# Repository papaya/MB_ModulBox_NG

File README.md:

# MB_ModulBox_NG — Contrôleur MIDI Modulaire (Écosystème MIDIbox NG)

> **Construisez votre propre contrôleur MIDI modulaire.**  
> MB_ModulBox_NG rassemble des front-ends originaux et des ré-implémentations KiCad de modules MIDIbox. Les niveaux de validation et les fichiers de fabrication disponibles varient d'une carte à l'autre : consulter la matrice ci-dessous avant toute commande.

---

## 🎯 Le projet en bref

MB_ModulBox_NG est une **bibliothèque de cartes de contrôle physiques** pour le système MIDIbox NG. Les sources, schémas, PCB et fichiers de fabrication ne sont pas tous disponibles pour chaque carte. Les états indiqués ci-dessous décrivent les fichiers présents dans le dépôt, pas une certification de fabrication.

Les **modules standards MIDIbox** (AIN, DIN, DOUT, Core, IO) sont fournis en **bonus de référence** pour alimenter ces front-ends — ils ne sont pas le cœur du projet. L'essence de ce dépôt, ce sont les **`custom-frontends/`**.

## 🧩 Les modules: Custom Front-ends — le cœur du dépôt

| Apercu | Module | Dossier | Fonction / bus | Fichiers de fabrication versionnés | État documentaire |
|---|---|---|---|---|---|
|   | encoders-led-rgb | [`custom-frontends/encoders-led-rgb/`](custom-frontends/encoders-led-rgb/) | 8 PEC16, DIN, 128 WS2812 | BOM/positions/netlist uniquement ; pas de Gerbers de sous-cartes | Prototype ; DRC et séparation à revoir |
|   | 4x-faders | [`custom-frontends/4x-faders/`](custom-frontends/4x-faders/) | 8 faders, AIN (`+3V0`) | Gerbers + perçages pour deux PCB ; pas de BOM dans `production/` | Fichiers disponibles, non certifiés |
|    | keysw-4x2 | [`custom-frontends/keysw-4x2/`](custom-frontends/keysw-4x2/) | 8 touches, DIN + 8 SK6812 adressables | BOM/positions/netlist ; pas de Gerbers | Sources à vérifier avant fabrication |
|  | 8x-pots | [`custom-frontends/8x-pots/`](custom-frontends/8x-pots/) | 8 potentiomètres, AIN (`+3V0`) | Gerbers + perçages ; exports BOM/netlist | Variante Pot-X2 à vérifier séparément |
|  | 8x-buttons | [`custom-frontends/8x-buttons/`](custom-frontends/8x-buttons/) | 8 boutons et 8 LED, DIN + DOUT | Gerbers + perçages + BOM | Fichiers disponibles, non certifiés |
|    | pad-rgb | [`custom-frontends/pad-rgb/`](custom-frontends/pad-rgb/) | 8 contacts, DIN + 8 WS2812 en cascade adressable | Positions + datasheet ; pas de Gerbers/BOM | non fonctionel , rebond , a coriger |
|    | oled-128x64 | [`custom-frontends/oled-128x64/`](custom-frontends/oled-128x64/) | SSD1309, SPI | BOM/positions/netlist ; pas de Gerbers | Sources à vérifier avant fabrication |
|    | carte-puissance | [`custom-frontends/carte-puissance/`](custom-frontends/carte-puissance/) | Distribution passive des rails | BOM/positions/netlist + PDF ; pas de Gerbers | Vérifier courant et routage |
|    | surface-control | [`custom-frontends/surface-control/`](custom-frontends/surface-control/) | SCS sur GPIO Core32F4 | Aucun fichier de production | Prototype non routé |

## Modules standards MIDIbox — ré-implémentations KiCad

| Type | Module | Dossier | Référence ucapps.de | Fichiers de fabrication versionnés |
|---|---|---|---|---|
|   | Core32F4 | [`standard-modules/Core/`](standard-modules/Core/) | [CORE_STM32F4](https://www.ucapps.de/mbhp_core_stm32f4.html) | BOM/positions/netlist ; pas de Gerbers |
|  | AIN / AINSER64 | [`standard-modules/AIN/`](standard-modules/AIN/) | [AINSER64](https://www.ucapps.de/mbhp_ainser64.html) | Sources KiCad et fichiers de production absents |
|  | DIN | [`standard-modules/DIN/`](standard-modules/DIN/) | [DIN](https://www.ucapps.de/mbhp_din.html) | Gerbers + perçages + BOM |
|  | DOUT | [`standard-modules/DOUT/`](standard-modules/DOUT/) | [DOUT](https://www.ucapps.de/mbhp_dout.html) | BOM/positions/netlist ; pas de Gerbers |
|  | MIDI IO | [`standard-modules/IO/`](standard-modules/IO/) | [MIDIbox NG Hardware](https://www.ucapps.de/midibox_ng_manual_hw.html) | Pas de fichiers de fabrication ; PCB non routé |
---

---

---
## 🚀 Démarrage rapide

1. **Cloner le dépôt**
   ```bash
   git clone https://github.com/papaya/MB_ModulBox_NG.git
   cd MB_ModulBox_NG
   ```

2. **Ouvrir un front-end dans KiCad**
   - Choisissez une carte dans `custom-frontends/` (ex: `4x-faders/`)
   - Ouvrez le fichier `.kicad_pro` avec KiCad (v9 recommandé)

3. **Lier les bibliothèques partagées**
   - `sym-lib-table` → `Mes_Librairies_KiCad/symbols/`
   - `fp-lib-table` → `Mes_Librairies_KiCad/footprints/`
   (chemins relatifs via `${KIPRJMOD}`)

4. **Fabriquer**
   - Vérifiez d'abord que la matrice ci-dessus indique des Gerbers et perçages pour la carte choisie.
   - Ouvrez les Gerbers dans un visualiseur indépendant et comparez-les au PCB KiCad avant commande.
   - Ne commandez pas une carte marquée prototype, non routée ou sans Gerbers ; un BOM/netlist seul n'est pas un jeu de fichiers de fabrication.
   - Les modèles 3D et fichiers sources supplémentaires, lorsqu'ils existent, sont sur l'[archive Google Drive](https://drive.google.com/drive/folders/1vpTdcTHLqAW1HyvYF8Y5nkU0c3LeNErb?usp=sharing).

## Guide maker : assemblage et commande des PCB

1. Choisissez un module dont la matrice indique des Gerbers et lisez son README avant de fabriquer.
2. Vérifiez le nombre de couches, le contour, les ouvertures de masque, les perçages PTH/NPTH et l'orientation des composants dans les fichiers de production.
3. Transmettez au fabricant les couches et fichiers de perçage publiés pour la carte choisie. Ne modifiez pas l'épaisseur de cuivre, le stack-up ou les dimensions sans revoir les contraintes électriques et mécaniques.
4. Utilisez la BOM et le fichier de positions uniquement s'ils sont publiés pour cette carte ; comparez références, valeurs et empreintes avec le schéma KiCad.
5. Assemblez hors tension, contrôlez les courts-circuits d'alimentation au multimètre, puis alimentez avec une alimentation limitée en courant.
6. Pour les cartes WS2812, utilisez une alimentation 5 V dimensionnée pour la charge et une masse commune. Le Core ne fournit pas l'alimentation des LED.

La présence de Gerbers ne certifie pas une carte ni ne garantit l'absence de défauts. Consultez les avertissements DRC/ERC et les limites propres à chaque README.

## 📦 Contenu de ce dépôt Git (et ce qui n'y est pas)

Ce dépôt est **allégé** pour rester léger et rapide à cloner. Sont versionnés :

| ✅ Inclus | Détail |
|---------|--------|
| Schémas KiCad | `.kicad_sch`, `.kicad_pro` (sources de conception) |
| PCB KiCad | `.kicad_pcb` (fichiers de routage) |
| Gerbers / perçages | Seulement pour les modules explicitement marqués dans la matrice ci-dessus |
| Bibliothèques partagées | `Mes_Librairies_KiCad/` (symboles `.kicad_sym` + empreintes `.pretty`) |
| Documentation & rendus | `README.md`, `PLAN.md`, `common-docs/`, `docs/assets/` (vues 3D en PNG) |
| Outils | `tools/` (scripts de nettoyage, extraction, validation) |

| ❌ Non versionné | Raison |
|------------------|--------|
| `*.wrl`, `*.stl`, `*.step`, `*.FCStd`, `*.dxf` | **CAO 3D volumineuse** (fichiers SolidWorks / Blender / FreeCAD / Wrl) — inutile pour KIcad, mais dépasse la limite de taille de GitHub |
| `archive/sources/` | **Copie brute de sauvegarde** (2,9 Go) des sources d'origine, en doublon — les versions maîtresses sont dans `standard-modules/` et `custom-frontends/` |
| `*.zip` | Archives de fabrication compressées — contenu identique aux gerbers présents |
| Fichiers de cache KiCad | `.kicad_prl`, `.bak`, `__pycache__` — régénérables |

> 📥 **Les fichiers 3D et les sources complètes** sont disponibles via l'archive Google Drive : [ALL FILES — Archive complète](https://drive.google.com/drive/folders/1vpTdcTHLqAW1HyvYF8Y5nkU0c3LeNErb?usp=sharing)
>
> Les modèles 3D manquants peuvent aussi être récupérés via **kicad-cli / KiCad 3D Viewer** directement depuis les bibliothèques officielles (kicad-footprints, kicad-symbols).

## 📖 Articles et ressources du blog ksir-diy.blogspot.com

| Article du blog | Thème | Lien |
|-----------------|-------|------|
| [ModulBox V2](https://ksir-diy.blogspot.com/2023/05/modulbox-v2.html) | Présentation globale du projet (mai 2023) | [Voir sur le blog](https://ksir-diy.blogspot.com/) |
| [ALL FILES — Archive complète](https://drive.google.com/drive/folders/1vpTdcTHLqAW1HyvYF8Y5nkU0c3LeNErb?usp=sharing) | Tous les fichiers de fabrication, schémas, Gerbers | [Google Drive](https://drive.google.com/drive/folders/1vpTdcTHLqAW1HyvYF8Y5nkU0c3LeNErb?usp=sharing) |

**Articles par carte :**
| Carte | Article du blog | Dossier |
|-------|----------------|---------|
| 4X2-POTS-v0.2 | Potentiomètres rotatifs | [`8x-pots`](custom-frontends/8x-pots/README.md) |
| 4X1-FAD-1-v0.2 / 4X1-FAD-2-v0.2 | Faders / glissières | [`4x-faders`](custom-frontends/4x-faders/README.md) |
| 4x2-BPL-v0.2 | Boutons poussoirs | [`8x-buttons`](custom-frontends/8x-buttons/README.md) |
| 4X2-PADS-RGB | Pads rétroéclairés RGB WS2812 | [`pad-rgb`](custom-frontends/pad-rgb/README.md) |
| 4X2 ENC-SW-16-LED-RING-RGB (PEC16) | Encodeurs avec anneau LED RGB | [`encoders-led-rgb`](custom-frontends/encoders-led-rgb/README.md) |

---

## ⚡ Modules standards MIDIbox (bonus de référence)

Ces modules standards alimentent les front-ends en bus AIN / DIN / DOUT. Ils sont fournis à titre de référence — ce ne sont pas la raison d’être de ce dépôt.

| Module | Bus | Rôle | Détail |
|--------|-----|------|--------|
| AIN | AIN (SPI `J19`) | Entrées analogiques (64 voies, AINSER64) | [📄 README](standard-modules/AIN/README.md) — ⚠️ **sources KiCad absentes** |
| DIN | DIN (`J8J9`) | 32 entrées digitales (4 × 74HC165) | [📄 README](standard-modules/DIN/README.md) |
| DOUT | DOUT (`J8J9`) | 32 sorties digitales (4 × 74HC595) | [📄 README](standard-modules/DOUT/README.md) |
| Core | — | Cœur STM32F4 (Core32F4), 4 lignes WS2812 | [📄 README](standard-modules/Core/README.md) |
| IO | MIDI | Interface MIDI 2 IN / 2 OUT (6N138) | [📄 README](standard-modules/IO/README.md) — ⚠️ **PCB non routé** |

---
> ⚠️ **Note importante sur les LEDs RGB WS2812/WS2812B :** Les cartes `encoders-led-rgb`, `pad-rgb` et `keysw-4x2` utilisent des LEDs adressables qui se connectent en **1 fil de données sur une sortie WS2812 du Core STM32F4** (`J4A` broches 6/8 = PB10/PB11, `J4B` broches 6/8 = **PB6 (TIM4)**/PB9) — **PAS** sur le bus DOUT (74HC595). Voir les README respectifs et [spécifications WS2812 MIOS32](https://www.midibox.org/mios32/midibox_ng/group___w_s2812.html).
>
> ℹ️ Sur les cartes encodeurs, pads et clavier, les LED sont montées **en cascade série** et adressables individuellement depuis une ligne de données.
---
## Licences, crédits et conditions d'utilisation

Ce dépôt contient deux catégories de matériel distinctes :

### 1. Modules standards officiels (`standard-modules/`)
**Core, AIN, DIN, DOUT, IO** — Ces modules sont des ré-implémentations sous KiCad basées sur les schémas originaux de la plateforme **MIDIbox (MBHP)** conçue par **Thorsten Klose / ucapps.de**.  
Crédits : Thorsten Klose & ucapps.de.  
Usage : strictement personnel, éducatif et DIY — **Non-Commercial**.

### 2. Modules et front-ends originaux (`custom-frontends/`)
**4x-faders, 8x-pots, 8x-buttons, encoders-led-rgb, pad-rgb, keysw-4x2, carte-puissance, oled-128x64, surface-control** — Cartes d'interface originales conçues pour l'écosystème **MB MODULBOX NG**, compatibles selon leur README avec les bus et modules MIDIbox NG.  
Usage indiqué dans les README : DIY/personnel ; les conditions de redistribution et d'utilisation commerciale restent à formaliser.

> **Licence non publiée :** le dépôt ne contient actuellement aucun fichier `LICENSE`. Les conditions applicables aux ré-implémentations des modules MIDIbox et aux créations originales doivent être clarifiées séparément avant toute redistribution ou utilisation commerciale. Les mentions DIY/non-commercial des README ne remplacent pas une licence formelle.

> **Badge OSHWA non affiché :** une restriction non-commerciale n'est pas une licence open-source matérielle conforme à la définition OSHWA. Il faut d'abord publier des conditions cohérentes, avec attribution et périmètre distincts pour les dérivés MIDIbox et les créations originales.

La documentation de brochage des bus s'appuie sur les pages officielles [MIDIbox NG Hardware](https://www.ucapps.de/midibox_ng_manual_hw.html), [DIN](https://www.ucapps.de/mbhp_din.html), [DOUT](https://www.ucapps.de/mbhp_dout.html), [AINSER64](https://www.ucapps.de/mbhp_ainser64.html) et [Core STM32F4](https://www.ucapps.de/mbhp_core_stm32f4.html). Les brochages des cartes custom sont décrits à partir des sources KiCad locales ; ne pas extrapoler le brochage officiel à un connecteur custom sans vérification.

---

## Documentation

- 📄 [`common-docs/README.md`](common-docs/README.md) — Hub de la documentation générale
- 📄 [`common-docs/bus-midibox-ng.md`](common-docs/bus-midibox-ng.md) — Schéma de principe des bus AIN, DIN et DOUT de MIDIbox NG
- 📁 [`common-docs/connecteurs/`](common-docs/connecteurs/) — Brochage détaillé des connecteurs de bus
- Chaque module standard et chaque front-end possède un README dans son dossier, avec ses limites et les fichiers disponibles
- 🖼️ [`docs/assets/`](docs/assets/) — Rendus 3D des PCB (vues top et isométrique)
- 🗺️ [`PLAN.md`](PLAN.md) — Feuille de route complète du projet (phases 0-10)
---
Retrouvez plus de photos sur **[Ksir DIY'S](https://ksir-diy.blogspot.com/)** — article principal : *"ModulBox V2" (mai 2023)*.

---

---

## ⚠️ Avertissement

> **Ce projet n'est pas réalisé par un professionnel.** Les fichiers schématiques, PCB, gerbers et documentations publiés ici sont issus d'un travail amateur, réalisé sur mon temps libre, à des fins personnelles et pédagogiques uniquement.
>
> **L'utilisation de ces fichiers ne m'engage à rien.** Aucune garantie de conformité, de sécurité, de fonctionnalité n'est donnée, ni implicitement ni explicitement.
>
> **Il peut y avoir des erreurs** : schématiques incomplètes, erreurs de routage, valeurs de composants inadaptées, impédances non respectées, alimentation insuffisante, isolation électrique non garantie, défauts de sérigraphie, etc. Certaines cartes listées ici sont explicitement marquées comme **non fonctionnelles** ou non testées.
>
> **À vos risques et périls.** Vous êtes seul responsable de la fabrication, de l'assemblage, de la mise sous tension et de l'utilisation des fichiers de ce dépôt. Vérifiez systématiquement les schémas, les contraintes de fabrication (épaisseurs de cuivre, empilages, clearances), les chaînages de masse et les tensions avant de fabriquer.
>
> Les droits et conditions de redistribution ne sont pas établis par ce dépôt tant qu'un fichier de licence n'est pas publié. Ce projet **n'est pas un support technique, ni un service de conception, ni une référence industrielle**.

---

## Contribuer

Consulter [`CONTRIBUTING.md`](CONTRIBUTING.md) avant de proposer une modification. Les signalements de défauts matériels doivent inclure le chemin du projet, la version de KiCad, le rapport DRC/ERC et les fichiers Gerber concernés.

---

**Crédits des modules standards :** Thorsten Klose & ucapps.de.  
**Conception des front-ends :** MB MODULBOX NG.> ⚠️ **Avertissement :** documentation de passion, **non professionnelle**. Fournie **sans garantie ni engagement**, **sans support technique**. Des **erreurs sont possibles** (schémas, valeurs, câblage, routage). À vos risques et périls : vérifiez tout avant de fabriquer et de mettre sous tension. Le détail complet de l'avertissement figure en fin de fichier.

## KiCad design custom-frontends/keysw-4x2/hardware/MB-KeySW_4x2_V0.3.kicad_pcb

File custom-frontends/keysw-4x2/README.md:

# keysw-4x2 — Module custom clavier 8 touches (DIN) + rétroéclairage SK6812 en cascade

## Description
Carte de front-end intégrant un clavier de **8 touches mécaniques** (Cherry MX) pour l'envoi d'evenements MIDI (notes, CC, etc.). Chaque touche est lue sur une entrée digitale distincte du bus DIN. La carte embarque en outre **8 LED RGB SK6812MINI-E adressables** montées **en cascade série** (chaque LED est adressable individuellement).

Ce module est une **conception originale MB MODULBOX NG** (conception Ksir), compatible avec les bus et modules du système MIDIbox NG. Ce n'est **pas** un module officiel MIDIbox.

## Specifications techniques
- 8 touches mécaniques **Cherry MX Low Profile** (`CHERRY MX1B-52NA`)
- **Interface DIN : 8 touches = 8 entrees 1:1** d'un registre 74HC165 (aucune matrice colonnes/lignes)
- **8 × SK6812MINI-E** en **cascade serie** : `J2` (entree DATA) -> D0 -> D1 -> ... -> D7 -> `J3` (sortie DATA)
- 8 × condensateur de decoupling 100 nF (1206) sur chaque LED
- Aucun registre a decalage, aucun CI de logique sur la carte

## Composants principaux
| Type | Dénomination | Qté |
|------|-------------|-----|
| Switch mécanique | Cherry MX Low Profile (`SW_Alps_Matias_1.00u_cherry_LP`) | 8 |
| LED RGB adressable | SK6812MINI-E (PLCC4) | 8 |
| Condensateur | C 100 nF 1206 | 8 |
| Connecteur | IDC Header 2x05 P2.54mm (`J1` = DIN, `J2` = entree LED, `J3` = sortie LED) | 3 |
| Connecteur | PinHeader 1x02 (`J4`, masse) | 1 |
| Touches (keycaps) | `beschr. Kappe.wrl` | 8 |

> ⚠️ **Corrections par rapport aux versions anterieures de cette page** :
> - Le clavier **n'est pas matriciel** : 8 touches = 8 entrees distinctes.
> - **Aucune diode anti-ghosting (1N4148) n'est presente dans le schema** : il n'y en a pas dans le composant. Le câblage 1:1 ne le requiert pas.
> - Les LED SK6812 sont **adressees individuellement** : chaque pixel peut afficher sa propre couleur. Elles sont câblees en serie (chaine) pour le câblage physique, chacune decodifie sa propre couleur (R,G,B).

## Brochage / Mapping MIDIbox NG

### `J1` —  entrees DIN (vers le module DIN 74HC165, chainage `J8`/`J9` du Core)
| Broche | Signal | Description |
|--------|--------|-------------|
| 1 | `J1-vss` | Masse commune (reliee a `J4` et GND) |
| 2 | — | Non connectee |
| 3 | `J1-D7` | Touche **SW7** |
| 4 | `J1-D6` | Touche **SW6** |
| 5 | `J1-D5` | Touche **SW5** |
| 6 | `J1-D4` | Touche **SW4** |
| 7 | `J1-D3` | Touche **SW3** |
| 8 | `J1-D2` | Touche **SW2** |
| 9 | `J1-D1` | Touche **SW1** |
| 10 | `J1-D0` | Touche **SW0** |

> Chaque touche est un contact **entre sa broche `J1-Dx` et la masse** (`J1` broche 1 / `J4`). Le niveau haut est assure par le pull-up 10 kΩ du module **DIN**.

### `J2` — entree de la cascade LED (vers la sortie WS2812 du Core)
| Broche | Signal | Description |
|--------|--------|-------------|
| 1 | GND | Masse |
| 2 a 5, 7, 8, 9 | — | Non connectees |
| 6 | `D0-DI` | **DATA d'entree** de la cascade (vers `D0`) |
| 10 | +5V | Alimentation des LED |

### `J3` — sortie de la cascade LED (vers la carte suivante ou vers le Core)
| Broche | Signal | Description |
|--------|--------|-------------|
| 1 | GND | Masse |
| 2 a 5, 7, 8, 9 | — | Non connectees |
| 6 | `D7-DO` | **DATA de sortie** de la cascade (depuis `D7`) |
| 10 | +5V | Alimentation des LED |

### `J4` — masse supplementaire
| Broche | Signal | Description |
|--------|--------|-------------|
| 1 | `J1-vss` | Relie a la masse des boutons |
| 2 | GND | Masse du plan |

### Chaine WS2812 du Core
Le **data** part d'une sortie WS2812 du **Core32F4** puis traverse toute la cascade :

```
Core (J4A/J4B, WS2812)  ->  J2 (broche 6)  ->  D0 -> D1 -> ... -> D7  ->  J3 (broche 6)
```

- Le Core STM32F4 dispose de **4 lignes WS2812** (`J4A` PB10 / PB11, `J4B` **PB6** = TIM4, reference MIOS32 / `J4B` PB9), chacune avec un pull-up 2,2 kΩ et une sortie en open-drain.
- **L'alimentation +5V des LED doit etre fournie separement** (les LED ne doivent pas etre alimentees via `J4A`/`J4B` du Core : jusqu'a 20 mA par LED RGB). Voir [specifications WS2812 MIOS32](https://www.midibox.org/mios32/midibox_ng/group___w_s2812.html).
- Comme les LED sont **cascadees**, chaque LED decode et affiche sa propre couleur (une seule ligne de donnees suffit).identique.

## Documentation de fabrication
- `hardware/` : sources KiCad (`MB-KeySW_4x2_V0.3.*`)
- `hardware/3D/shapes3D/` : modèles 3D des touches et switchs (`.wrl`)
- `production/` : Gerbers, BOM (`bom.csv`), fichiers de position, archives de fabrication

## Assets de visualisation
| Type | Fichier | Description |
|------|---------|-------------|
| Top view | `3d-top.png` | Vue de dessus du PCB |
| Iso 3D | `3d-iso.png` | Vue isométrique avec composants |

---

## Conception & Compatibilité

Carte d'interface **originale MB MODULBOX NG** (conception Ksir), compatible avec les bus et modules du système MIDIbox NG. Ce n'est **pas** un module officiel MIDIbox.

> **Origine et usage :** conception originale MB MODULBOX NG, prévue pour le DIY/personnel. Aucune licence formelle n'est publiée dans le dépôt ; voir le README racine. **Aucune garantie ni engagement** n'est fourni sur la justesse du câblage ou du routage.
> ⚠️ **Avertissement :** documentation de passion, **non professionnelle**. Fournie **sans garantie ni engagement**, **sans support technique**. Des **erreurs sont possibles** (schémas, valeurs, câblage, routage). À vos risques et périls : vérifiez tout avant de fabriquer et de mettre sous tension. Le détail complet de l'avertissement figure en fin de fichier.

🔋 **Gestion de la puissance** : La gestion de la puissance des LED est indispensable, j'ai paramétré les LED à 10% de puissance.
Conception originale MB MODULBOX NG. > ⚠️ **Avertissement :** documentation de passion, **non professionnelle**. Fournie **sans garantie ni engagement**, **sans support technique**. Des **erreurs sont possibles** (schémas, valeurs, câblage). À vos risques et périls : vérifiez tout avant de fabriquer et de mettre sous tension.

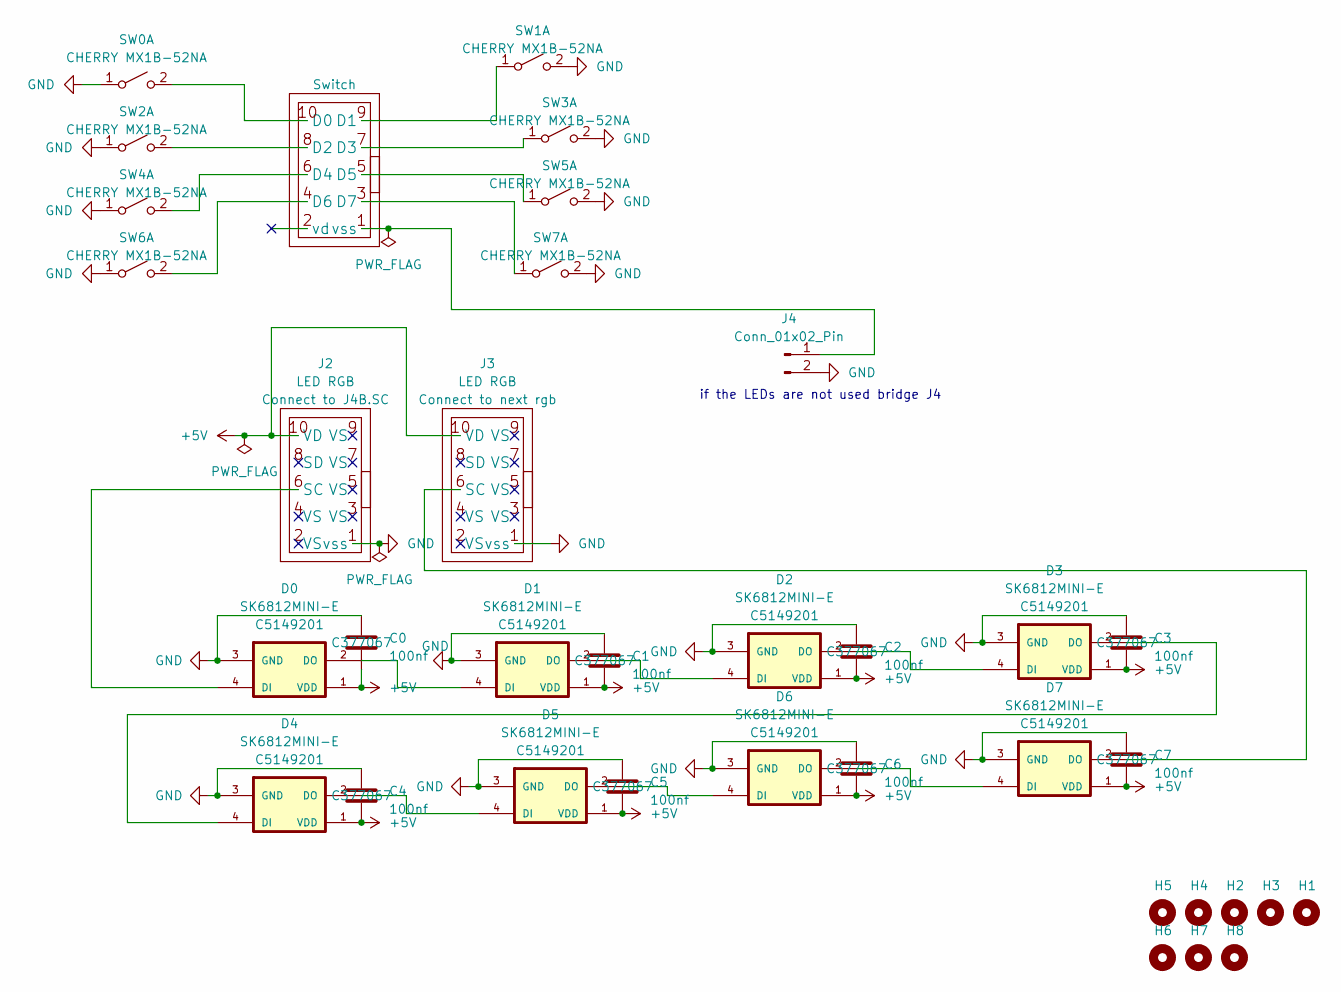
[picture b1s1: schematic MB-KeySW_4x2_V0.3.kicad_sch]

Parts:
C0, C1, C2, C3, C4, C5, C6, C7: 100nf; C_1206_3216Metric; JLCPCB Part # C377067
D0, D1, D2, D3, D4, D5, D6, D7: SK6812MINI-E; SK6812-MINI-E; JLCPCB Part # C5149201
H1, H2, H3, H4, H5, H6, H7, H8: MountingHole; MountingHole_3mm
J1, J2, J3: IDC-Header_2x05_P2.54mm_Vertical
J4: Conn_01x02_Pin; PinHeader_1x02_P2.54mm_Vertical
SW0, SW1, SW2, SW3, SW4, SW5, SW6, SW7: CHERRY MX1B-52NA; SW_Alps_Matias_1.00u_cherry_LP

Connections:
+5V: C0.2, C1.2, C2.2, C3.2, C4.2, C5.2, C6.2, C7.2, D0.1 (VDD), D1.1 (VDD), D2.1 (VDD), D3.1 (VDD), D4.1 (VDD), D5.1 (VDD), D6.1 (VDD), D7.1 (VDD), J2.10 (VD), J3.10 (VD)
GND: C0.1, C1.1, C2.1, C3.1, C4.1, C5.1, C6.1, C7.1, D0.3 (GND), D1.3 (GND), D2.3 (GND), D3.3 (GND), D4.3 (GND), D5.3 (GND), D6.3 (GND), D7.3 (GND), J2.1 (vss), J3.1 (vss), J4.2, SW0.1 (A), SW1.2 (B), SW2.1 (A), SW3.2 (B), SW4.1 (A), SW5.2 (B), SW6.1 (A), SW7.2 (B)
unnamed: D0.4 (DI), J2.6 (SC)
unnamed: D0.2 (DO), D1.4 (DI)
unnamed: D1.2 (DO), D2.4 (DI)
unnamed: D2.2 (DO), D3.4 (DI)
unnamed: D3.2 (DO), D4.4 (DI)
unnamed: D4.2 (DO), D5.4 (DI)
unnamed: D5.2 (DO), D6.4 (DI)
unnamed: D6.2 (DO), D7.4 (DI)
unnamed: D7.2 (DO), J3.6 (SC)
unnamed: J1.10 (D0), SW0.2 (B)
unnamed: J1.9 (D1), SW1.1 (A)
unnamed: J1.8 (D2), SW2.2 (B)
unnamed: J1.7 (D3), SW3.1 (A)
unnamed: J1.6 (D4), SW4.2 (B)
unnamed: J1.5 (D5), SW5.1 (A)
unnamed: J1.4 (D6), SW6.2 (B)
unnamed: J1.3 (D7), SW7.1 (A)
unnamed: J1.1 (vss), J4.1

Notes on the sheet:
if the LEDs are not used bridge J4

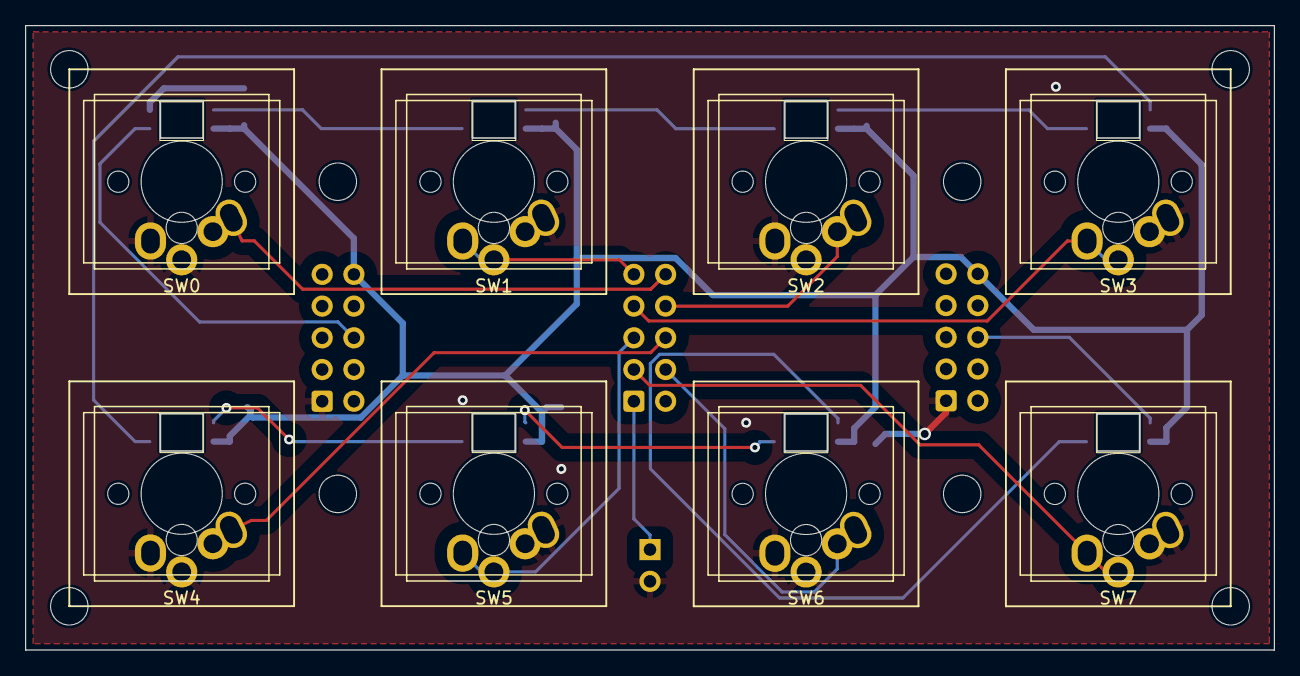
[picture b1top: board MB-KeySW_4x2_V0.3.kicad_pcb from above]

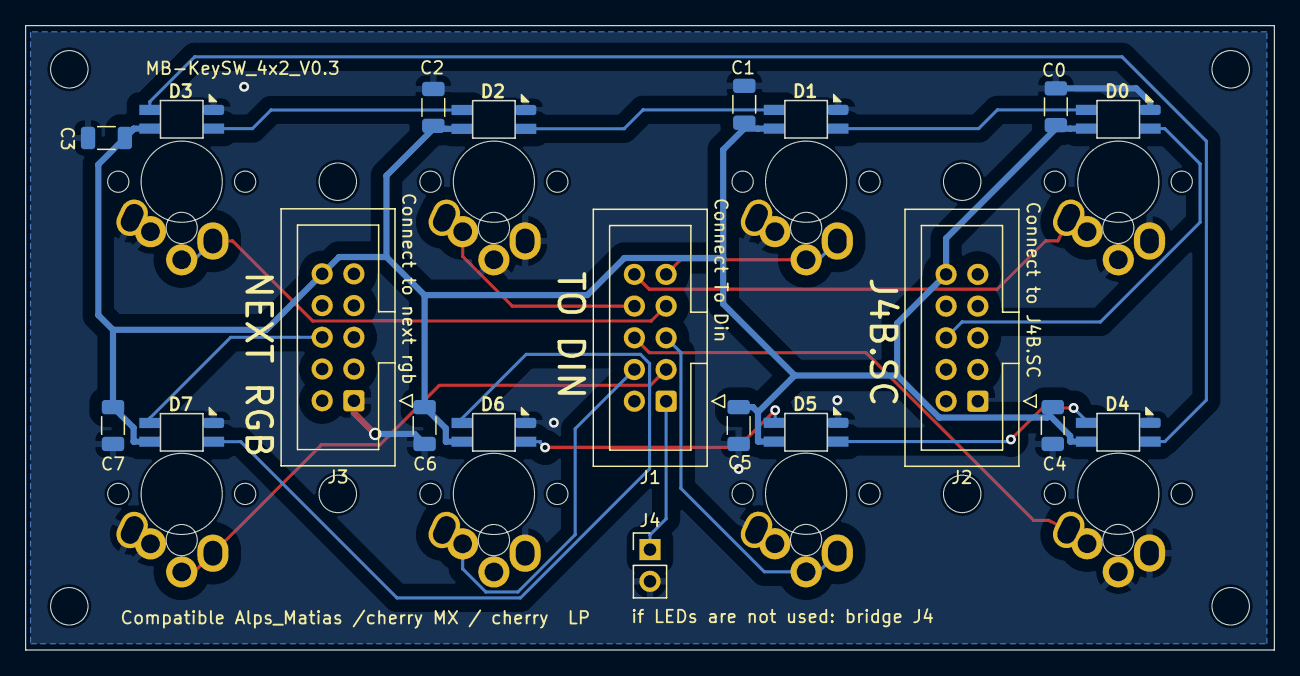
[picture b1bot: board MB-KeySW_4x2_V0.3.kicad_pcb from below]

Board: 2 copper layers, 100.0 x 50.0 mm, 36 parts (20 on the bottom side), 20 nets.

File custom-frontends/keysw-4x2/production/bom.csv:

Designator,Footprint,Quantity,Value,LCSC Part #
"C0, C1, C2, C3, C4, C5, C6, C7",1206,8,100nf,C377067
"D0, D1, D2, D3, D4, D5, D6, D7",SK6812-MINI-E,8,SK6812MINI-E,C5149201
"H1, H2, H3, H4, H5, H6, H7, H8",MountingHole_3mm,8,MountingHole,
"J1, J2, J3",IDC-Header_2x05_P2.54mm_Vertical,3,IDC-Header_2x05_P2.54mm_Vertical,
J4,PinHeader_1x02_P2.54mm_Vertical,1,Conn_01x02_Pin,
"SW0, SW1, SW2, SW3, SW4, SW5, SW6, SW7",SW_Alps_Matias_1.00u_cherry_LP,8,CHERRY MX1B-52NA,

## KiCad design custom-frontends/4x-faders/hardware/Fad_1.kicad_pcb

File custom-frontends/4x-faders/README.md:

# 4x-faders — Module custom faders / glissières (AIN)

## Description

Carte de front-end intégrant des faders (glissières) pour le contrôle continu de paramètres MIDI (volume, filtre, effets, etc.). Chaque fader est lu sur une voie analogique indépendante. La carte ne contient **aucun convertisseur analogique-numérique** : elle expose les curseurs sur un connecteur IDC, reliés au module **AINSER64** (MCP3208 + CD4051) du bus AIN.

Le répertoire contient **deux cartes complémentaires** :
- `Fad_1` : 4 faders, connecteurs `J3` (curseurs) et `J4` (passage)
- `Fad_2` : 4 faders, connecteur `J5` (curseurs)

## Spécifications techniques

- 4 faders (glissières) par carte, courbe linéaire **RA6020F-10-15F2-B10K** (10 kΩ)
- **Tension de référence : +3V0** (et non +5V) — la borne `+3V0` alimente les deux extrémités de chaque fader
- Sortie : curseurs + GND + +3V0 sur connecteur **IDC 2x05 P2.54mm**
- Lecture : via le module **AINSER64** du bus AIN (broche `J19` du Core32F4, SPI)
- Aucune résistance, aucun condensateur, aucun circuit actif sur la carte

## Composants principaux

| Type | Dénomination | Qté (par carte) |
|------|-------------|-----|
| Fader / glissière | ALPS RA6020F-10-15F2-B10K (10 kΩ) | 4 |
| Connecteur | IDC Header 2x05 P2.54mm Vertical | 1 à 2 |
| Bouton/pommeau de fader | `ALPS Fader Knob.wrl` | 4 |
| Vis de fixation | MountingHole 3.2mm M3 | 4 |

## Brochage / Mapping MIDIbox NG

### `Fad_1` — connecteur `J3` (curseurs)

| Broche | Signal | Description |
|--------|--------|-------------|
| 1 | GND | Masse commune (référence 0 V) |
| 2 | +3V0 | Alimentation des faders (borne haute) |
| 3 | `J3-A7` | Curseur de **fad6** |
| 4 | `J3-A6` | Curseur de **fad5** |
| 5 | `J3-A5` | Curseur de **fad7** |
| 6 | `J3-A4` | Curseur de **fad8** |
| 7 | `J3-A3` | Curseur de **fad6** (idem broche 3) |
| 8 | `J3-A2` | Curseur de **fad5** (idem broche 4) |
| 9 | `J3-A1` | Curseur de **fad7** (idem broche 5) |
| 10 | `J3-A0` | Curseur de **fad8** (idem broche 6) |

Le connecteur `J4` de `Fad_1` est un **connecteur de passage** : il reproduit les mêmes 8 signaux que `J3` (broches 3 à 6), GND (broches 1, 2) et +3V0 (broches 1, 2) ; ses broches 7 à 10 sont libres. Il permet de chaîner plusieurs cartes.

### `Fad_2` — connecteur `J5` (curseurs)

| Broche | Signal | Description |
|--------|--------|-------------|
| 1 | GND | Masse commune |
| 2 | +3V0 | Alimentation des faders |
| 3 | `J5-A7` | Curseur de **fad1** |
| 4 | `J5-A6` | Curseur de **fad2** |
| 5 | `J5-A5` | Curseur de **fad3** |
| 6 | `J5-A4` | Curseur de **fad4** |
| 7 à 10 | — | Non connectées |

> **Câblage du fader (vérifié dans le schéma KiCad)** : patte 1 → GND, patte 2 → **curseur** (→ broche `J3`/`J5` correspondante), patte 3 → **+3V0**.

> Le curseur étant relié à l'entrée analogique de l'AINSER64, la plage de mesure est **0 .. 3,0 V** (et non 0 .. 5 V).

> **Les entrées analogiques non utilisées de l'AINSER64 doivent être reliées à la masse**, sinon l'application émet des valeurs aléatoires.

### Module AINSER64 (rappel)

- Connecteur : **`J19`** du Core STM32F4 (SPI, 2 chip-selects `RC1`/`RC2`)
- Architecture : 1 × **MCP3208** (ADC 12 bits) + 8 × **CD4051** (multiplexeurs 8:1) + 1 × 74HC595
- Capacité : 64 entrées par module, jusqu'à 2 modules (128 voies) supportés par MIDIbox NG

## Documentation de fabrication

- `hardware/` : sources KiCad (`Fad_1.*`, `Fad_2.*`)
- `hardware/3D/` : modèles 3D des faders et boutons (`.wrl`)
- `production/` : Gerbers pour Fad_1 et Fad_2
- Blog : [4X1-FAD-1-v0.2 / 4X1-FAD-2-v0.2 sur ksir-diy.blogspot.com](https://ksir-diy.blogspot.com/)

## Assets de visualisation

| Type | Fichier | Description |
|------|---------|-------------|
| Top view | `3d-top.png` | Vue de dessus du PCB |
| Iso 3D | `3d-iso.png` | Vue isométrique avec composants |
| 3D quart | `3d%203quart.png` | Vue 3D quart du PCB |
---

## Conception & Compatibilité

Carte d'interface **originale MB MODULBOX NG** (conception Ksir), compatible avec les bus et modules du système MIDIbox NG. Ce n'est **pas** un module officiel MIDIbox.

> **Origine et usage :** conception originale MB MODULBOX NG, prévue pour le DIY/personnel. Aucune licence formelle n'est publiée dans le dépôt ; voir le README racine. **Aucune garantie ni engagement** n'est fourni sur la justesse du câblage ou du routage.

> ⚠️ **Avertissement :** documentation de passion, **non professionnelle**. Fournie **sans garantie ni engagement**, **sans support technique**. Des **erreurs sont possibles** (schémas, valeurs, câblage). À vos risques et périls : vérifiez tout avant de fabriquer et de mettre sous tension.

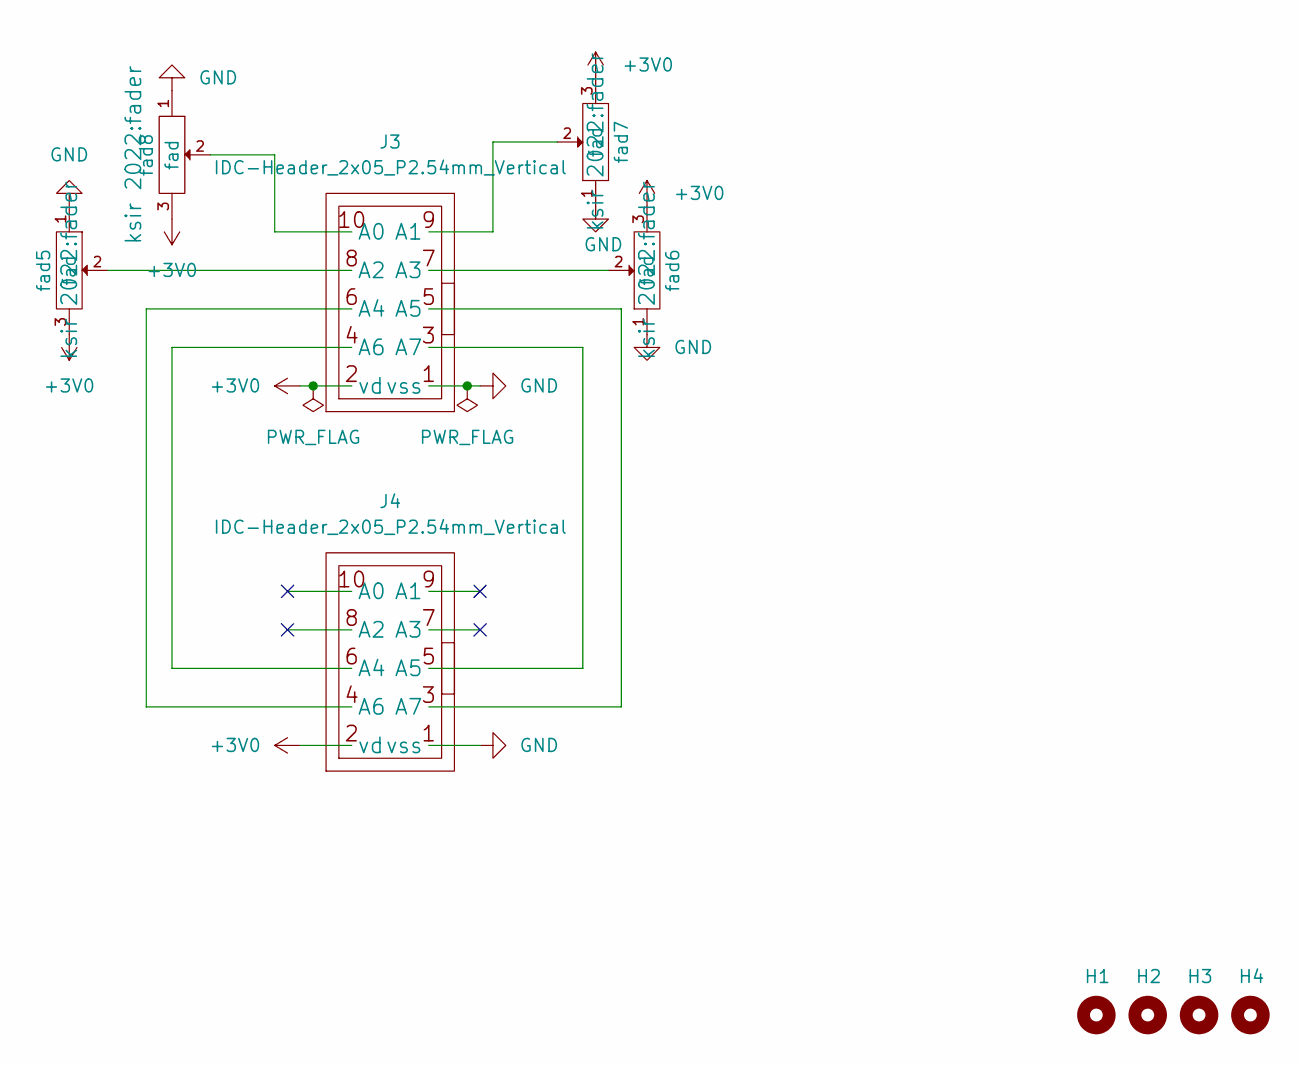
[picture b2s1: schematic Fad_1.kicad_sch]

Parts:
H1, H2, H3, H4: MountingHole; MountingHole_3.2mm_M3
J3, J4: IDC-Header_2x05_P2.54mm_Vertical
fad5, fad6, fad7, fad8: fad; fader

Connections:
+3V0: J3.2 (vd), J4.2 (vd), fad5.3 (vd), fad6.3 (vd), fad7.3 (vd), fad8.3 (vd)
GND: J3.1 (vss), J4.1 (vss), fad5.1 (vss_masse), fad6.1 (vss_masse), fad7.1 (vss_masse), fad8.1 (vss_masse)
unnamed: J3.10 (A0), fad8.2
unnamed: J3.9 (A1), fad7.2
unnamed: J3.8 (A2), fad5.2
unnamed: J3.7 (A3), fad6.2
unnamed: J3.6 (A4), J4.4 (A6)
unnamed: J3.5 (A5), J4.3 (A7)
unnamed: J3.4 (A6), J4.6 (A4)
unnamed: J3.3 (A7), J4.5 (A5)

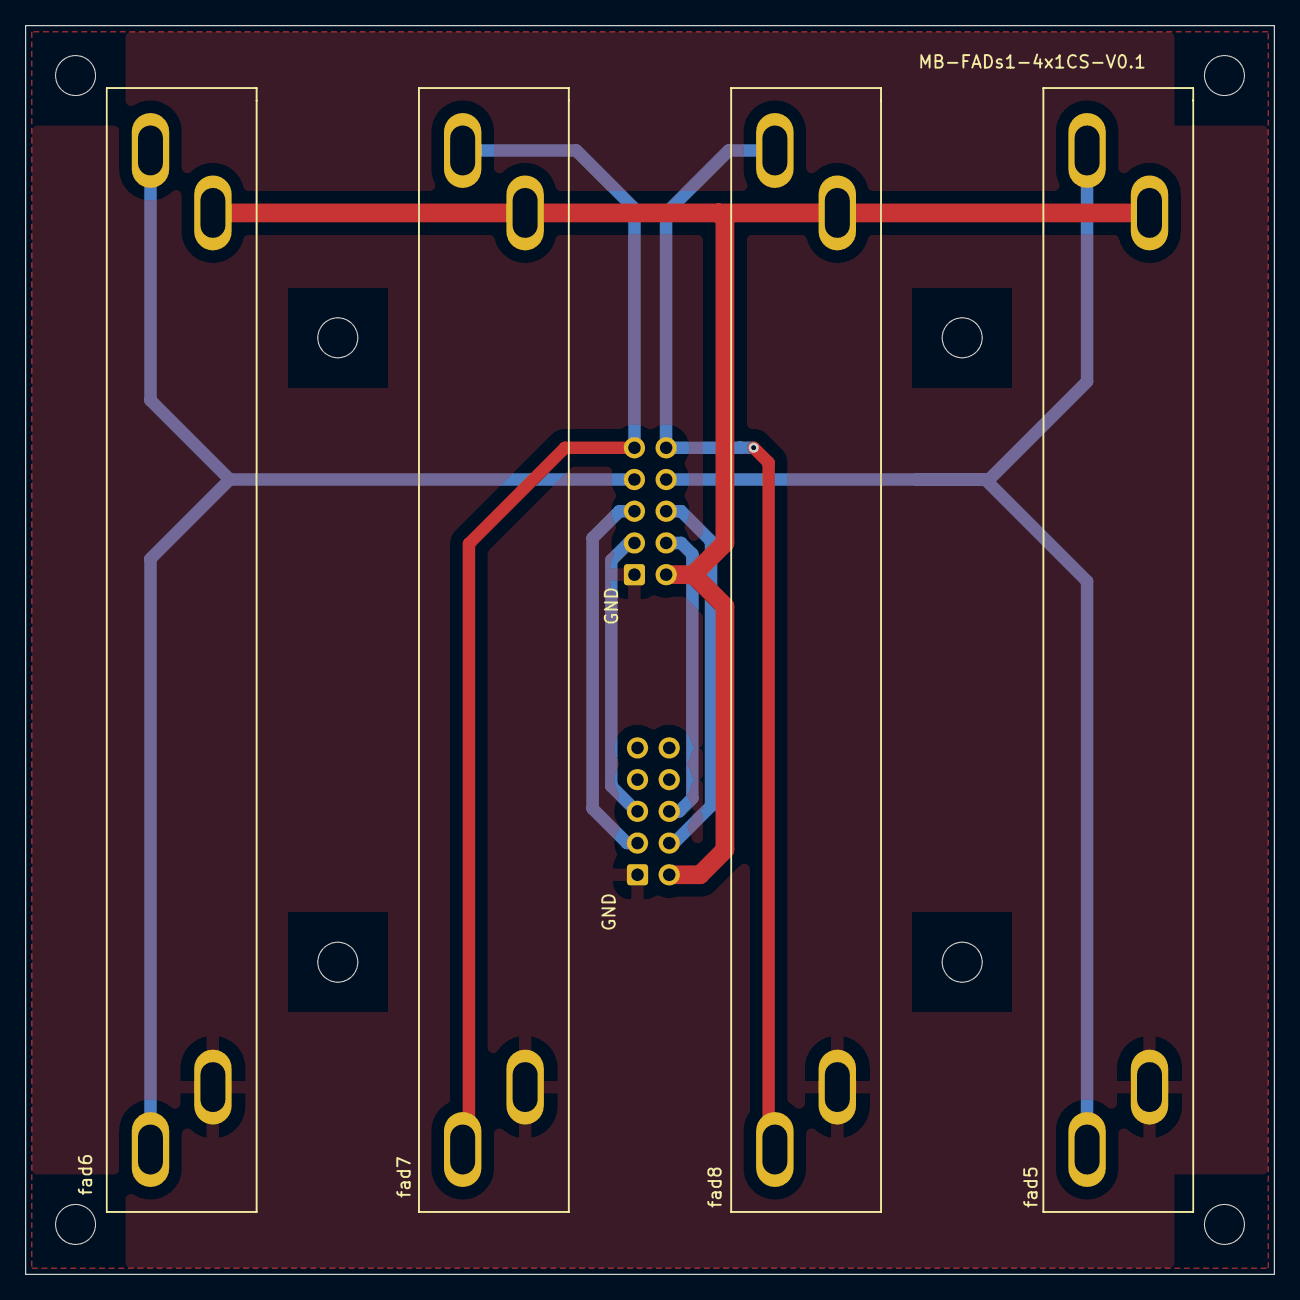
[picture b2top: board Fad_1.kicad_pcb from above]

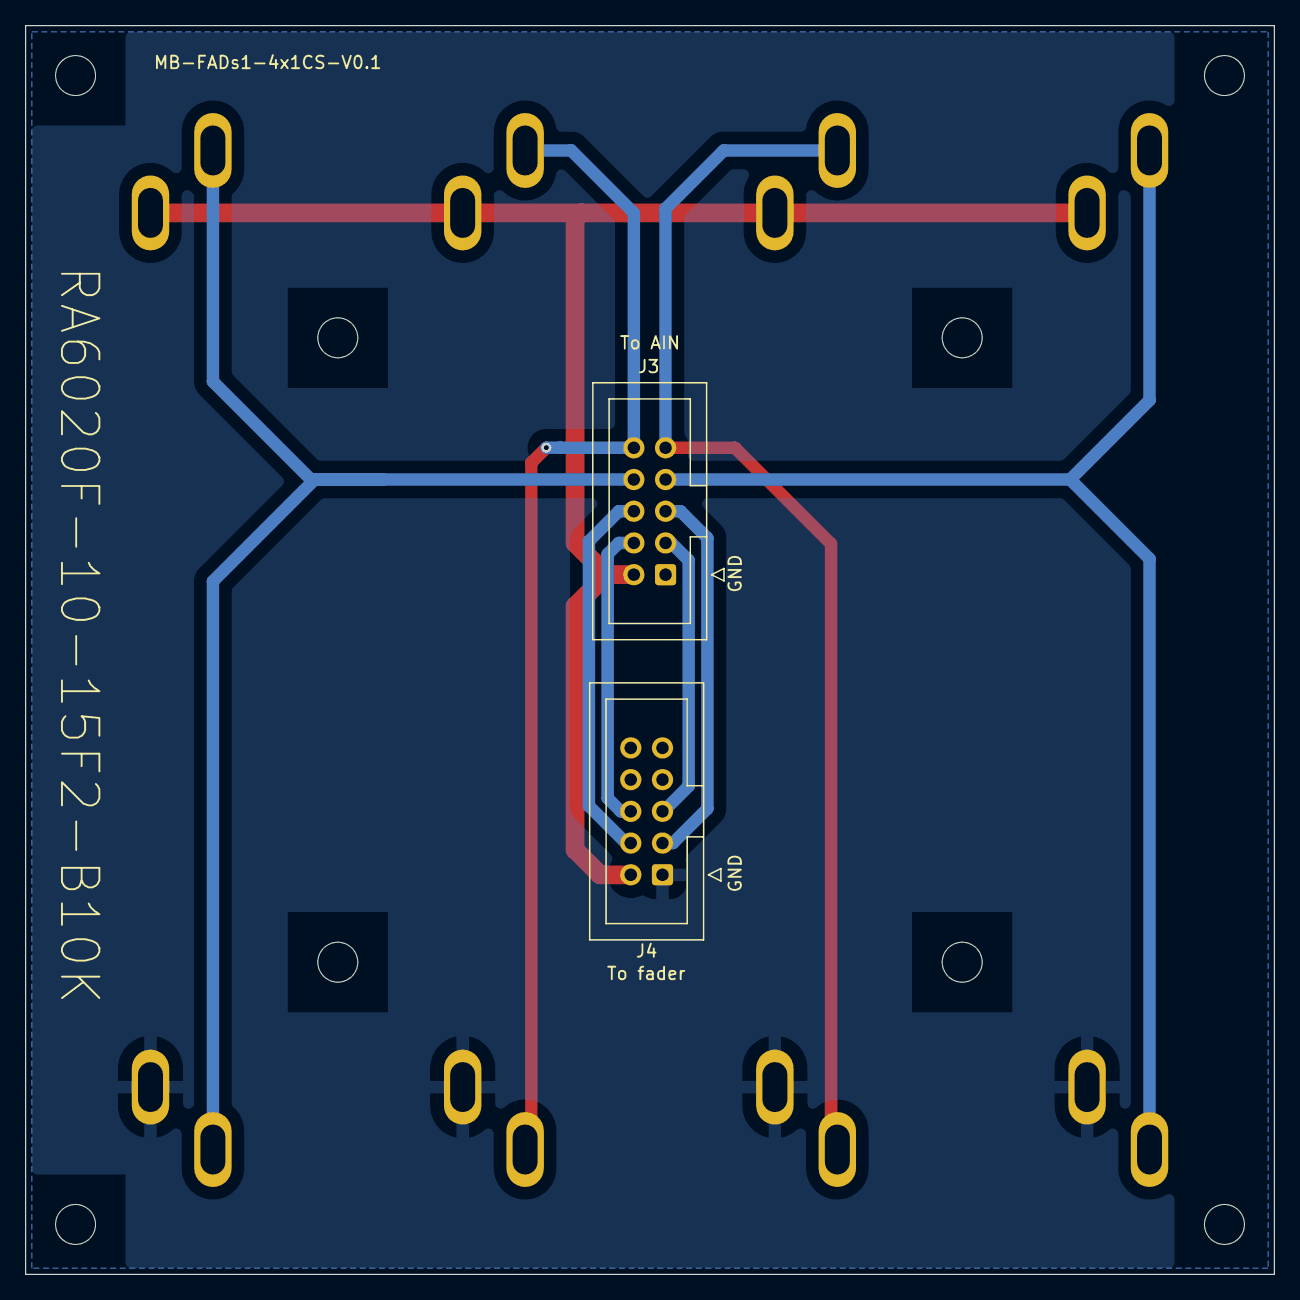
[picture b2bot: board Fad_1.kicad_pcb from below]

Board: 2 copper layers, 100.0 x 100.0 mm, 14 parts (2 on the bottom side), 10 nets.

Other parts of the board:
H1#2, H2#2, H3#2, H4#2: MountingHole; MountingHole_3.2mm_M3

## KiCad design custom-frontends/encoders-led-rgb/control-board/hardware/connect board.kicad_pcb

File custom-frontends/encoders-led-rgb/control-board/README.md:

# connect Board — interconnexion des encodeurs et du ring LED

Carte custom du système **MB MODULBOX NG**. Le PCB présent (`connect board.kicad_pcb`) est une carte de connectique : il ne contient pas les 74HC165, 74HC595 ou décodeurs décrits dans les anciennes versions de cette page. Aucun schéma autonome correspondant n'est fourni.

## Éléments réellement présents

- 3 connecteurs IDC 2x05 (`J11`, `J12`, `J13`) pour les signaux des encodeurs.
- 4 connecteurs 1x06 (`J30`..`J33`) raccordés aux groupes encodeurs de la carte `En`.
- Connecteurs 1x06 `J34`/`J35` et IDC 2x05 `J44`/`J45` pour alimentations et données du ring.
- Aucun composant de logique active.

## Brochage relevé dans le PCB

Pour `J11`..`J13`, broche 1 = GNDA, broche 2 = NC et broches 3..10 = signaux listés ci-dessous.

| Connecteur | Broches 3 à 10 |
|---|---|
| `J11` | `C_SW8`, `C_SW7`, `C_SW6`, `C_SW5`, `C_SW4`, `C_SW3`, `C_SW2`, `C_SW1` |
| `J12` | `C_ENC8B`, `C_ENC8A`, `C_ENC7B`, `C_ENC7A`, `C_ENC6B`, `C_ENC6A`, `C_ENC5B`, `C_ENC5A` |
| `J13` | `C_ENC4B`, `C_ENC4A`, `C_ENC3B`, `C_ENC3A`, `C_ENC2B`, `C_ENC2A`, `C_ENC1B`, `C_ENC1A` |

Les connecteurs `J30`..`J33` sont des groupes 6 broches :

| Connecteur | Broches 1 à 6 |
|---|---|
| `J30` | `C_SW1`, `C_SW2`, `C_ENC1B`, `C_ENC1A`, `C_ENC2B`, `C_ENC2A` |
| `J31` | `C_ENC3B`, `C_ENC3A`, `C_ENC4B`, `C_ENC4A`, `C_SW3`, `C_SW4` |
| `J32` | `C_ENC5B`, `C_ENC5A`, `C_ENC6B`, `C_ENC6A`, `C_SW5`, `C_SW6` |
| `J33` | `C_SW7`, `C_SW8`, `C_ENC7B`, `C_ENC7A`, `C_ENC8B`, `C_ENC8A` |

`J34` et `J35` reprennent respectivement `+5VA`/`+5VD`, un signal sur leur broche 2 et GNDA sur leur broche 3. Le signal de `J34` est reporté sur `J44` broche 6 ; celui de `J35` sur `J45` broche 6. `J44`/`J45` : broche 1 = GNDA, broche 10 = rail +5 V correspondant ; les autres broches sont NC sauf la broche 6.

## Projet et limites

- PCB : [`hardware/connect board.kicad_pcb`](hardware/connect%20board.kicad_pcb)
- Projet KiCad associé : [`hardware/connect board.kicad_pro`](hardware/connect%20board.kicad_pro)
- Schéma autonome : absent. Le schéma historique [`../hardware/PEC_16_V0.2.kicad_sch`](../hardware/PEC_16_V0.2.kicad_sch) reste la seule source schématique du système complet ; il n'a pas été scindé en feuilles vérifiées par sous-carte.
- Fabrication : aucun jeu Gerber propre à cette carte n'est versionné.

Les brochages ci-dessus sont extraits des nets du PCB, pas vérifiés par un schéma indépendant ni par un prototype. Vérifier la connectique et l'orientation des câbles avant branchement.

Cette carte est une création originale pour MB MODULBOX NG. Voir le README parent pour les conditions d'utilisation et l'état de licence du dépôt.

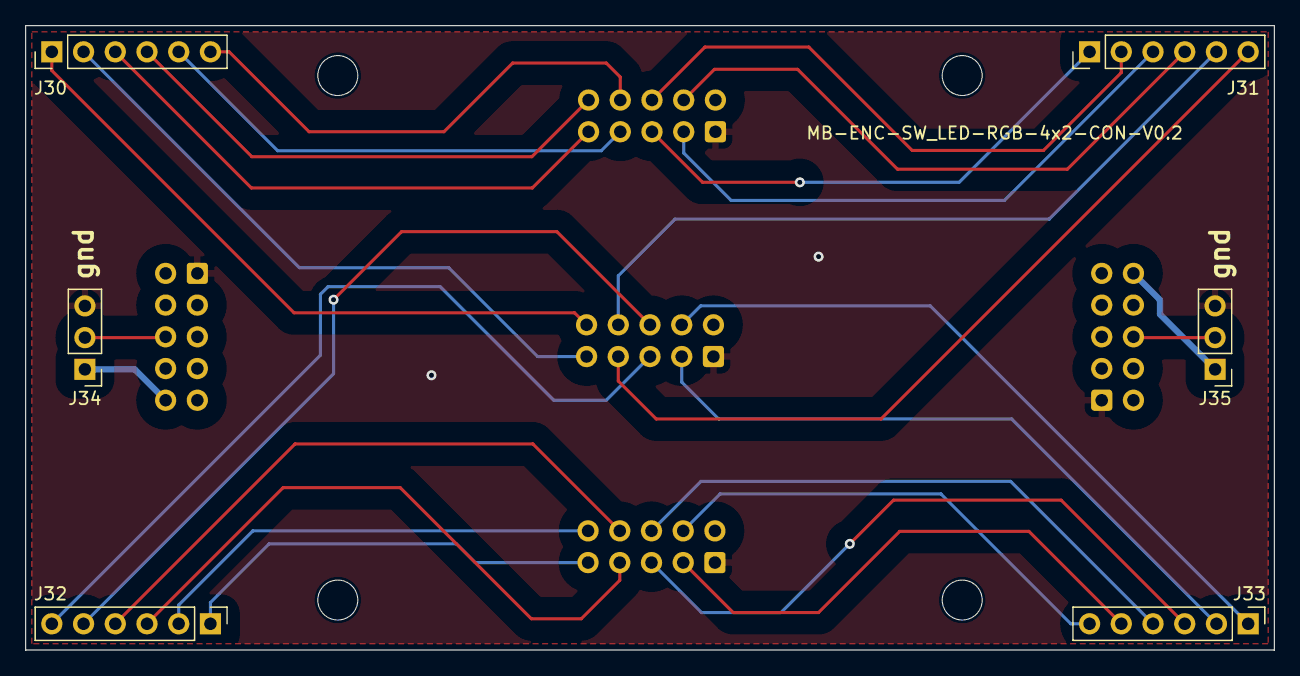
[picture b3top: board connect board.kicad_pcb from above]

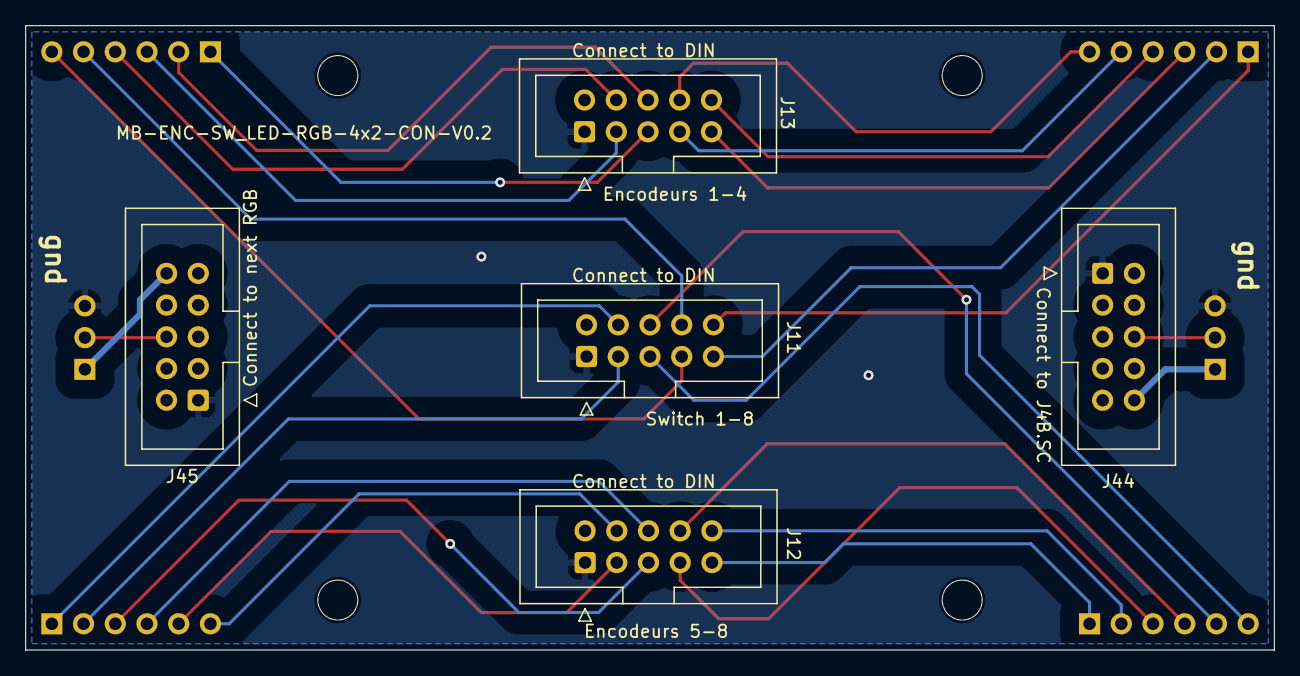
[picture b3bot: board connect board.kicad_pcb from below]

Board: 2 copper layers, 100.0 x 50.0 mm, 15 parts (5 on the bottom side), 29 nets.

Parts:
H14, H16, H18, H20: MountingHole; MountingHole_3.2mm_M3
J11, J12, J13: sin_in; IDC-Header_2x05_P2.54mm_Vertical_ksr_dIN
J30, J31, J32, J33: Conn_01x06_Pin; PinHeader_1x06_P2.54mm_Vertical
J34, J35: Conn_01x06_Pin; PinHeader_1x03_P2.54mm_Vertical
J44, J45: IDC-Header_2x05_P2.54mm_Vertical

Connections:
+5VA: J34.1, J44.10
+5VD: J35.1, J45.10
C_ENC1A: J13.10, J30.4
C_ENC1B: J13.9, J30.3
C_ENC2A: J13.8, J30.6
C_ENC2B: J13.7, J30.5
C_ENC3A: J13.6, J31.2
C_ENC3B: J13.5, J31.1
C_ENC4A: J13.4, J31.4
C_ENC4B: J13.3, J31.3
C_ENC5A: J12.10, J32.2
C_ENC5B: J12.9, J32.1
C_ENC6A: J12.8, J32.4
C_ENC6B: J12.7, J32.3
C_ENC7A: J12.6, J33.4
C_ENC7B: J12.5, J33.3
C_ENC8A: J12.4, J33.6
C_ENC8B: J12.3, J33.5
C_SW1: J11.10, J30.1
C_SW2: J11.9, J30.2
C_SW3: J11.8, J31.5
C_SW4: J11.7, J31.6
C_SW5: J11.6, J32.5
C_SW6: J11.5, J32.6
C_SW7: J11.4, J33.1
C_SW8: J11.3, J33.2
GNDA: J11.1, J12.1, J13.1, J34.3, J35.3, J44.1, J45.1
unnamed: J34.2, J44.6
unnamed: J35.2, J45.6

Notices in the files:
README.md:
License: à clarifier
